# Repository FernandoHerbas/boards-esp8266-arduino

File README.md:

# esp8266-arduino
## Repo de las siguientes placas:
### Controlador o placa de control con arduino nano y esp8266.
### De potencia, supone placa con 4 reles a 12V y 3 mosfet IRF530 usando transistores BC337, adaptable a ControlBoard. (Incompleto):
   > En tal caso dejo el esquema, el diseño del pcb es complejo dada las dimensiones y los encapsulados actuales, ademas el costo y tiempo es elevado para esta primera etapa del proyecto. La alternativa encontrada es comprar una placa de reles de 12V que vienen fabricadas y pensadas para arduino, el presupuesto es similar a la placa de potencia con solo los relé y demas componentes para su funcionamiento.
### Para el control de una tira de leds RGB 5050, hecha con mosfet IRF530, considero realizar esta placa ya que no se encuentra en el mercado.
    
:tada::fireworks:
link a lib
[esp8266](https://github.com/jdunmire/kicad-ESP8266).

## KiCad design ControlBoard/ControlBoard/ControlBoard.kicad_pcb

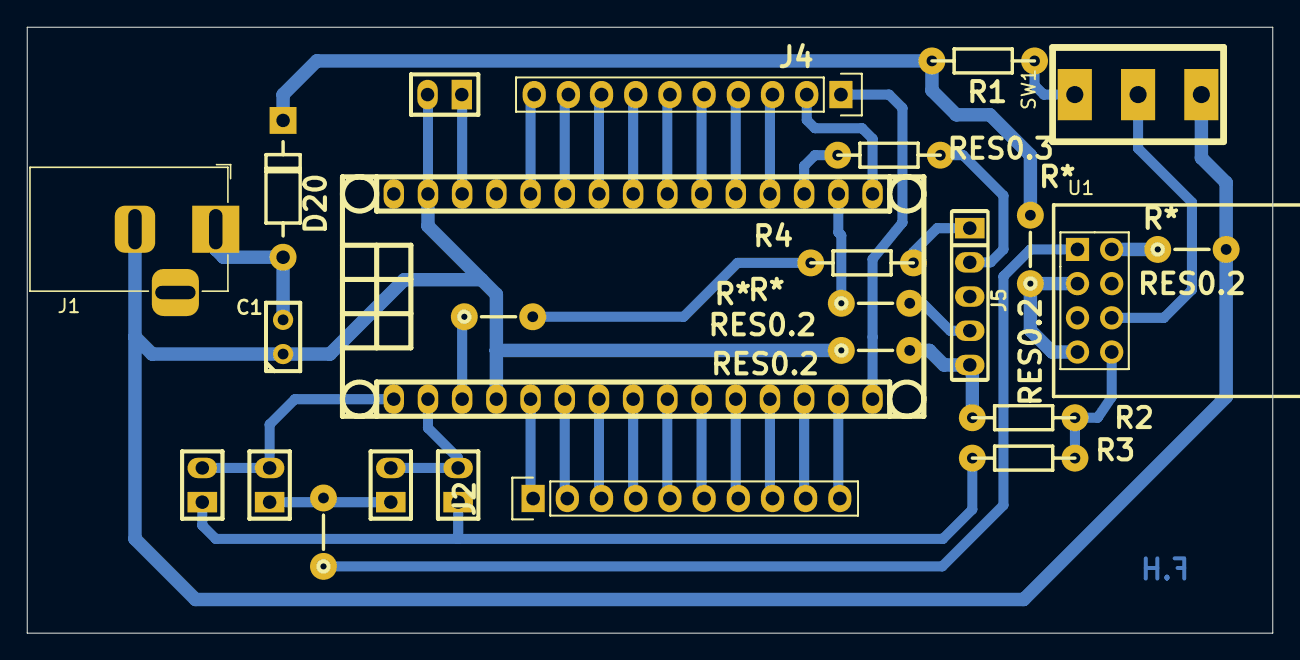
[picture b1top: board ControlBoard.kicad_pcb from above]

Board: 2 copper layers, 92.5 x 45.0 mm, 25 parts (0 on the bottom side), 34 nets.

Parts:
C1: C; CAP_0.1
D20: DIODE; DO-41
J1: Barrel_Jack_MountingPin; BarrelJack_Horizontal
J2, J4: HEADER_10; Pin_Header_Straight_1x10
J3: Arduino_Nano_Header; arduino_nano_header
J5: HEADER_5; Pin_Header_5
JP1, JP2, JP3, JP4, JP5: Jumper
R1: 10K; RES0.3
R2: 1K; RES0.3
R3: 2K7; RES0.3
R4: 0; RES0.3
RES0.2, RES0.2#2, RES0.2#3, RES0.2#4, RES0.2#5, RES0.2#6: R*; RES0.2
RES0.3: 0; RES0.3
SW1: SW_SPDT; SW_SPDT_TH_Vertical
U1: ESP-01v090; ESP-01

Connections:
+3V3: D20.2, R1.1, RES0.2.1, RES0.2.2, U1.3, U1.7
/3V3: J3.17, J5.4, RES0.2#5.1, RES0.2#5.2
/A0: J3.19, J4.3
/A1: J3.20, J4.4
/A2: J3.21, J4.5
/A3: J3.22, J4.6
/A4: J3.23, J4.7
/A5: J3.24, J4.8
/A6: J3.25, J4.9
/A7: J3.26, J4.10
/AREF: J3.18, J5.2, RES0.3.1, RES0.3.2
/D2: J2.1, J3.5
/D3: J2.2, J3.6
/D4: J2.3, J3.7
/D5: J2.4, J3.8
/D6: J2.5, J3.9
/D7: J2.6, J3.10
/D8: J2.7, J3.11
/D9: J2.8, J3.12
/D10: J2.9, J3.13
/D11: J2.10, J3.14
/D12: J3.15, J4.1
/D13: J3.16, J4.2
/GPIO0: SW1.2, U1.6
/RESET: J3.3, J5.1, R4.2, RES0.2#6.1, RES0.2#6.2
/RX: R2.2, R3.1, U1.8
/RX-A: JP1.1, JP3.1, R2.1
/TX: JP2.1, JP4.1, RES0.2#4.1, RES0.2#4.2, U1.1
GND: C1.1, J1.2, J3.4, J3.29, J5.5, JP5.2, R3.2, RES0.2#2.1, RES0.2#2.2, RES0.2#3.1, RES0.2#3.2, SW1.3, U1.2
unnamed: C1.2, D20.1, J1.1
unnamed: J3.1, JP1.2, JP2.2
unnamed: J3.2, JP3.2, JP4.2
unnamed: J3.28, JP5.1
unnamed: R1.2, SW1.1

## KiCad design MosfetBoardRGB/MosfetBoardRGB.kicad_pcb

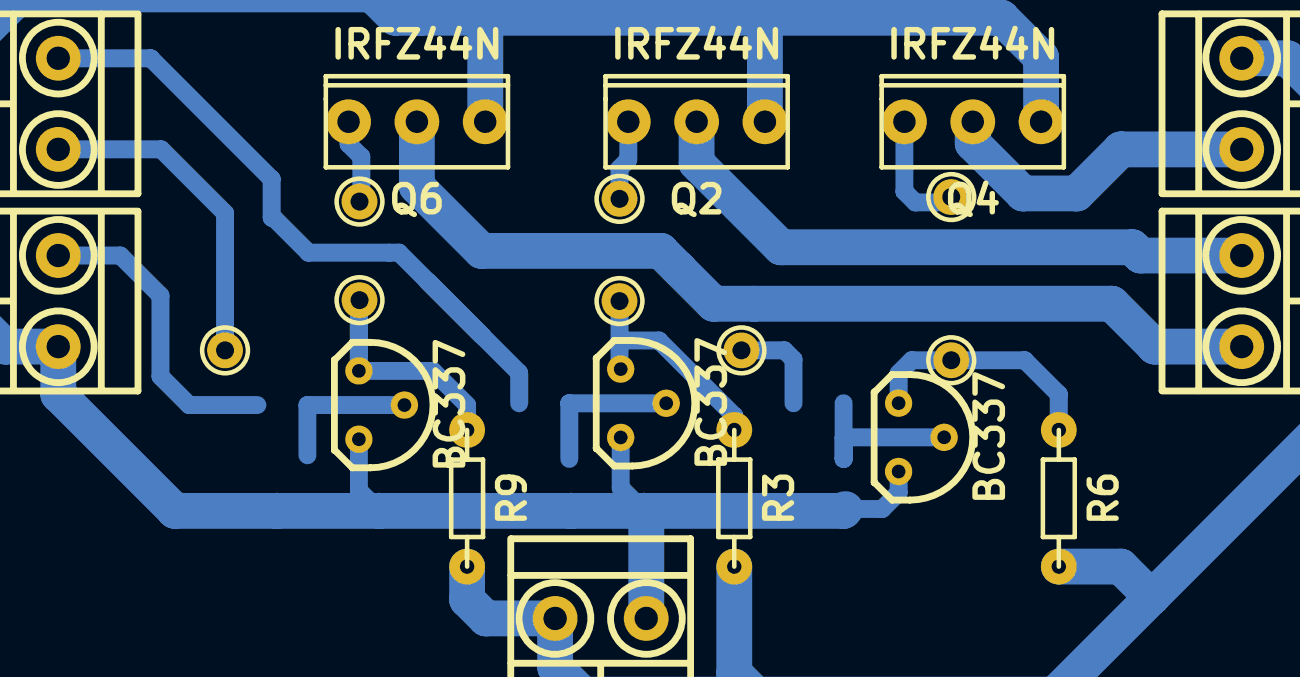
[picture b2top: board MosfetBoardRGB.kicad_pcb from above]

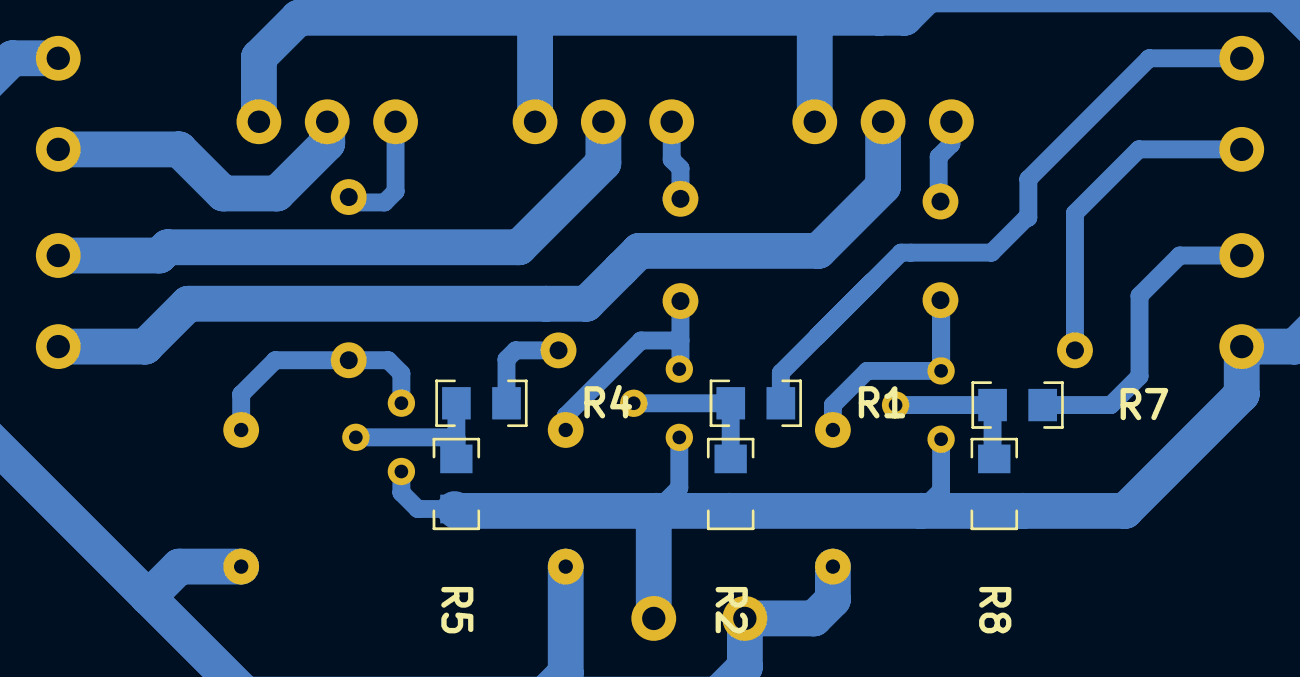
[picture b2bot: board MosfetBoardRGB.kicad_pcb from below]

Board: 2 copper layers, 28 parts (6 on the bottom side), 14 nets.

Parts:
J1, J2, J3, J4, J5: TB_1X2; BORNERA2_AZUL
Q1, Q3, Q5: BC337; to92
Q2, Q4, Q6: IRFZ44N; to220
R1, R4, R7: 4,7K; R_1206
R2, R5, R8: 100K; R_1206
R3, R6, R9: 4,7K; RES0.3
pad_1_5mm, pad_1_5mm#2, pad_1_5mm#3, pad_1_5mm#4, pad_1_5mm#5, pad_1_5mm#6, pad_1_5mm#7, pad_1_5mm#8: VAL**; pad_1_5mm

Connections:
+12V: J3.1, J4.2, R3.2, R6.2, R9.2
/B: J5.1, Q6.2
/G: J4.1, Q4.2
/PW0: J1.1, R1.2
/PW1: J1.2, R4.2, pad_1_5mm#2.1, pad_1_5mm#7.1
/PW2: J2.1, R7.2
/R: J5.2, Q2.2
GND: J2.2, J3.2, Q1.3, Q2.3, Q3.3, Q4.3, Q5.3, Q6.3, R2.2, R5.2, R8.2
unnamed: Q1.1, Q2.1, R3.1, pad_1_5mm#3.1, pad_1_5mm#6.1
unnamed: Q1.2, R1.1, R2.1
unnamed: Q3.1, Q4.1, R6.1, pad_1_5mm#4.1, pad_1_5mm#5.1
unnamed: Q3.2, R4.1, R5.1
unnamed: Q5.1, Q6.1, R9.1, pad_1_5mm.1, pad_1_5mm#8.1
unnamed: Q5.2, R7.1, R8.1

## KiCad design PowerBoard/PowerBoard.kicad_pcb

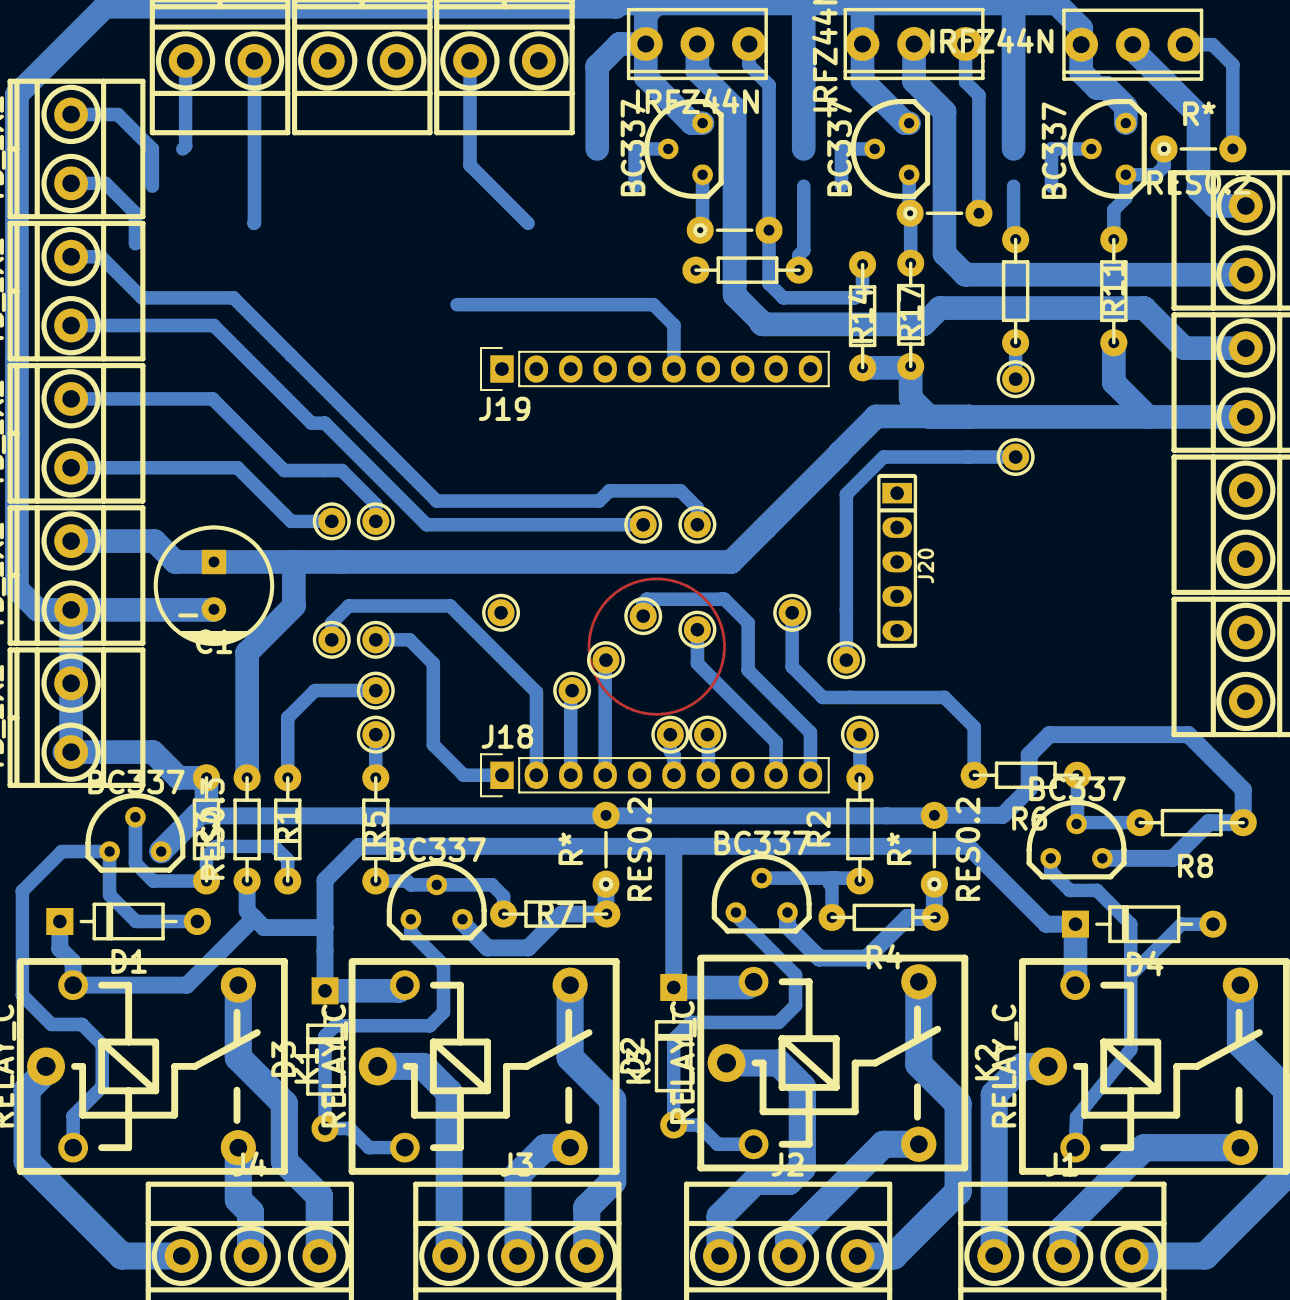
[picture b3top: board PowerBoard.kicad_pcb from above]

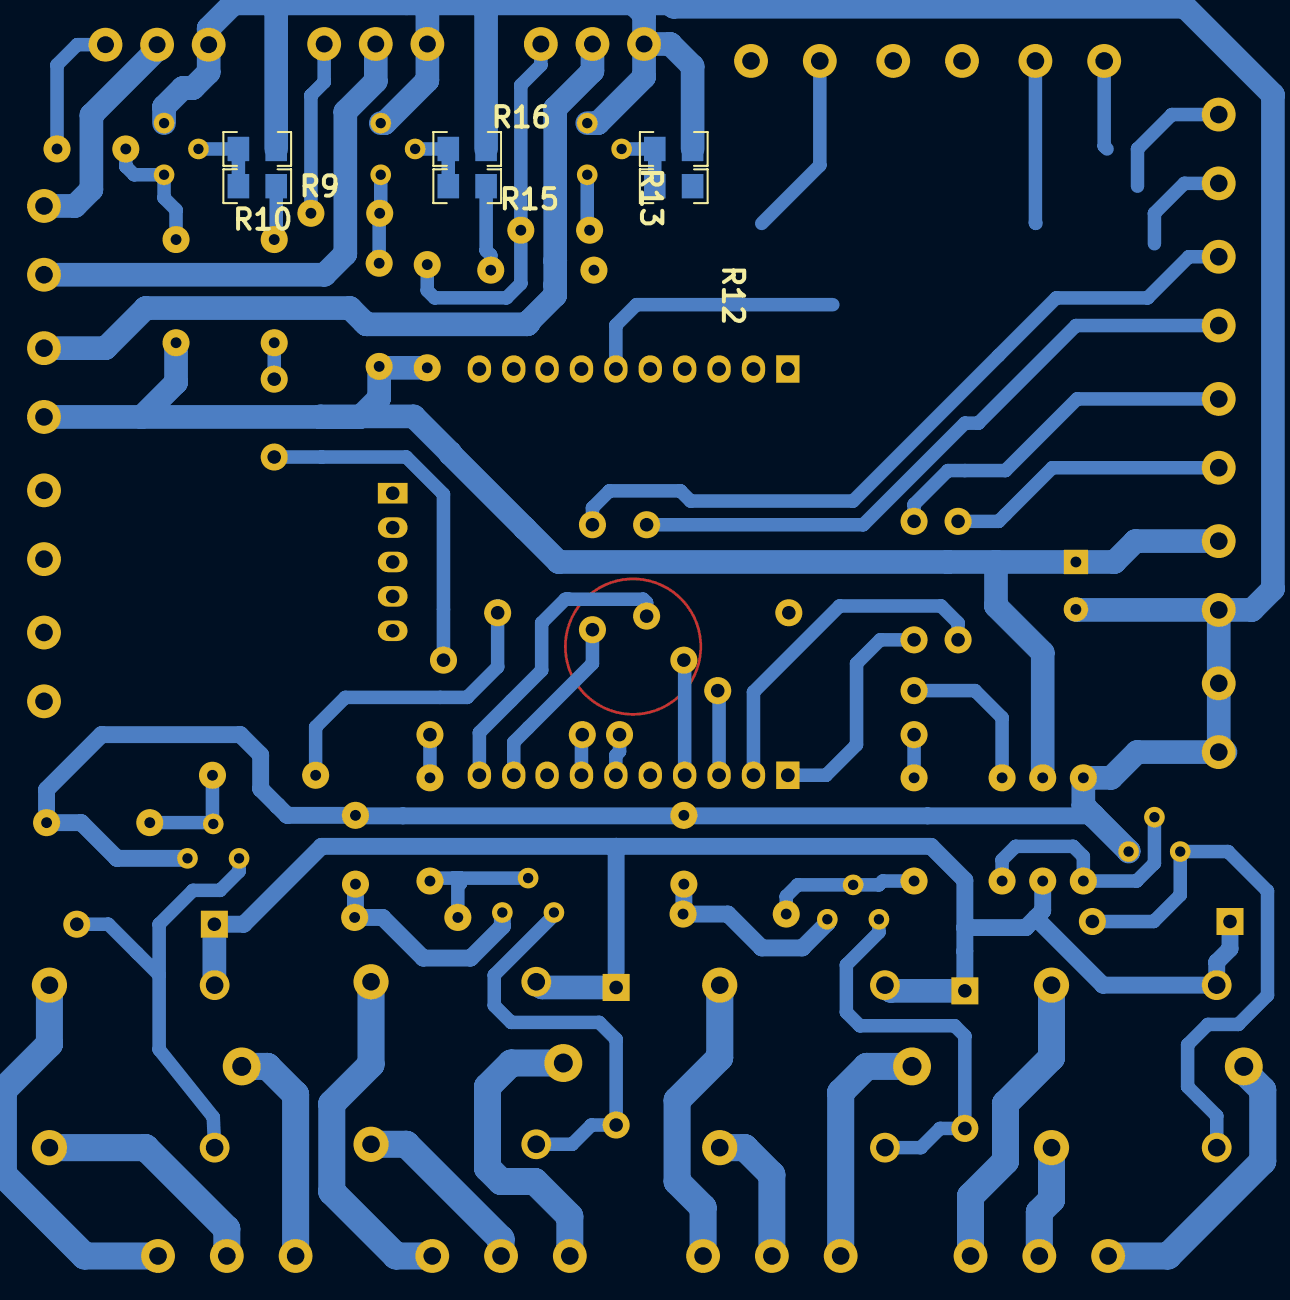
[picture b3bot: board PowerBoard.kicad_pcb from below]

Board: 2 copper layers, 79 parts (6 on the bottom side), 54 nets.

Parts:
C1: 10uF; CAP_ELEC_8x11.5mm
D1, D2, D3, D4: DIODE; DO-41
J1, J2, J3, J4: TB_1X3; BORNERA3
J7, J8, J9, J10, J11, J12, J13, J14, J15, J16, J17, J21: TB_1X2; BORNERA2
J18, J19: HEADER_10; Pin_Header_Straight_1x10
J20: HEADER_5; Pin_Header_5
K1, K2, K3, K4: RELAY_C; Relay_C
Q1, Q2, Q3, Q4, Q5, Q7, Q9: BC337; to92
Q6, Q8, Q10: IRFZ44N; to220
R1, R2, R5, R6, R11, R14, R17: 4,7K; RES0.3
R3, R4, R7, R8: 47K; RES0.3
R9, R12, R15: 4,7K; R_1206
R10, R13, R16: 100K; R_1206
RES0.2, RES0.2#2, RES0.2#3: R*; RES0.2
RES0.3: R*; RES0.3
pad_1_5mm, pad_1_5mm#2, pad_1_5mm#3, pad_1_5mm#4, pad_1_5mm#5, pad_1_5mm#6, pad_1_5mm#7, pad_1_5mm#8, pad_1_5mm#9, pad_1_5mm#10, pad_1_5mm#11, pad_1_5mm#12: VAL**; pad_1_5mm
pad_2mm, pad_2mm#2, pad_2mm#3, pad_2mm#4, pad_2mm#5, pad_2mm#6, pad_2mm#7, pad_2mm#8: VAL**; pad_2mm

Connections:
+12V: C1.1, D1.2, D2.2, D3.2, D4.2, J16.1, J21.1, K1.5, K2.5, K3.5, K4.5, R11.2, R14.2, R17.2, RES0.3.1, RES0.3.2
/3V3: J7.2, J20.4
/A4: J10.2, J19.7
/A5: J9.1, J19.8
/A6: J9.2, J19.9
/A7: J8.1, J19.10
/AREF: J7.1, J20.2
/B: J16.2, Q8.2
/BTN0: J14.1, J19.3
/BTN1: J14.2, J19.4
/BTN2: J13.1, J19.5
/BTN3: J13.2, J19.6
/D2: J12.1, J18.1, pad_2mm.1, pad_2mm#8.1
/D3: J12.2, J18.2, pad_2mm#2.1, pad_2mm#7.1
/D10: J11.1, J18.9, pad_1_5mm#2.1, pad_1_5mm#3.1
/D11: J11.2, J18.10, pad_1_5mm.1, pad_1_5mm#12.1
/D13: J10.1, J19.2
/G: J15.1, Q10.2
/LED0: J18.3, R1.2, pad_1_5mm#5.1, pad_1_5mm#10.1
/LED1: J18.6, R5.2, pad_1_5mm#6.1, pad_1_5mm#9.1
/LED2: J18.7, R2.2, pad_1_5mm#7.1, pad_1_5mm#8.1
/LED3: J19.1, R6.2, pad_1_5mm#4.1, pad_1_5mm#11.1
/PWM0: J18.4, R9.2, pad_2mm#3.1, pad_2mm#4.1, pad_2mm#5.1, pad_2mm#6.1
/PWM1: J18.5, R15.2
/PWM2: J18.8, R12.2
/R: J15.2, Q6.2
/RALED0: J4.2, K1.3
/RALED1: J3.2, K3.3
/RALED2: J2.2, K2.3
/RALED3: J1.2, K4.3
/RCLED0: J4.3, K1.4
/RCLED1: J3.3, K3.4
/RCLED2: J2.3, K2.4
/RCLED3: J1.3, K4.4
/RESET: J8.2, J20.1
/RLED0: J4.1, K1.1
/RLED1: J3.1, K3.1
/RLED2: J2.1, K2.1
/RLED3: J1.1, K4.1
GND: C1.2, J17.1, J17.2, J20.5, J21.2, Q1.3, Q2.3, Q3.3, Q4.3, Q5.3, Q6.3, Q7.3, Q8.3, Q9.3, Q10.3, R3.1, R4.1, R7.1, R8.1, R10.1, R13.1, R16.1, RES0.2.1, RES0.2.2, RES0.2#3.1, RES0.2#3.2
unnamed: D1.1, K1.2, Q1.1
unnamed: D2.1, K2.2, Q2.1
unnamed: D3.1, K3.2, Q3.1
unnamed: D4.1, K4.2, Q4.1
unnamed: Q1.2, R1.1, R3.2
unnamed: Q2.2, R2.1, R4.2
unnamed: Q3.2, R5.1, R7.2
unnamed: Q4.2, R6.1, R8.2
unnamed: Q5.1, Q6.1, R11.1, RES0.2#2.1, RES0.2#2.2
unnamed: Q5.2, R9.1, R10.2
unnamed: Q7.1, Q8.1, R14.1
unnamed: Q7.2, R12.1, R13.2
unnamed: Q9.2, R15.1, R16.2
unnamed: Q9.1, Q10.1, R17.1

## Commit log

2020-11-04 Agrego gitignore y proyecto de kicad
2020-12-08 Implemento esquema, la misma se alimenta con una fuente externa de 3v3 para el esp, no considero regulador ya que tengo una fuente con ese voltaje
2020-12-18 Agrego PCB + Comienzo de diseño
2020-12-19 Concluyo diseño de ControlBoard
2021-01-08 Comienzo esquema del circuito de potencia para arduinoNano
2021-01-12 Diseño de la placa al 70%. Considero nuevas alternativas a este proyecto.
2021-01-12 Placa mosfet RGB terminada
2021-01-16 Añado algunos modelos 3D
2021-03-31 6-Placa de control, creo proyecto + agrego esquema
